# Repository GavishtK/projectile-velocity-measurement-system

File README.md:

# Projectile Velocity Measurement System (PVMS)

> **Development of an IoT-Based Projectile Velocity Measurement System**

---

# 📖 Overview

The **Projectile Velocity Measurement System (PVMS)** is an embedded system designed to accurately measure projectile velocity using the **Optical Time-of-Flight (ToF)** principle.

The system employs two optical sensing gates connected to an **ESP32** microcontroller. As a projectile passes through the sensing gates, the ESP32 records the elapsed time with microsecond precision and calculates the projectile's velocity.

The measured velocity is displayed in real time on an OLED display and simultaneously transmitted through the Serial Monitor for debugging and data logging.

To improve hardware integration and reliability, a **custom PCB was designed using KiCad**, incorporating interfaces for the ESP32, OLED display, optical sensors, laser modules, and power connections.

This project was developed as part of a **summer internship at DRDO**. This repository contains only my original implementation, documentation, and hardware design intended for educational and portfolio purposes. No confidential or restricted information has been included.

---

# 📷 Project Preview

## Hardware Prototype

## OLED Display

## PCB Schematic

## PCB Layout

## PCB 3D Model

---

# ✨ Features

- High-speed projectile velocity measurement
- Optical Time-of-Flight sensing
- ESP32-based embedded system
- Microsecond precision using hardware interrupts
- Real-time OLED display
- Serial Monitor output
- Automatic timeout handling
- Low-cost implementation
- Custom KiCad PCB
- Compact and portable design

---

# ⚙ Hardware Used

| Component | Quantity |
|------------|----------|
| ESP32 DevKit V1 | 1 |
| SSD1306 OLED Display (128×64) | 1 |
| Laser Modules | 2 |
| Photodiodes | 2 |
| Breadboard | 1 |
| Jumper Wires | As Required |
| USB Power Supply | 1 |

---

# 🛠 Software Used

- Arduino IDE
- ESP32 Board Package
- KiCad
- Adafruit SSD1306 Library
- Adafruit GFX Library
- Wire Library

---

# 💻 PCB Design

A custom PCB was designed using **KiCad** to simplify wiring, improve reliability, and provide a compact hardware platform.

### PCB Features

- ESP32 interface
- OLED display connector
- Optical sensor connectors
- Laser module connectors
- Power input connector
- Compact PCB layout
- 3D STEP model included

---

# 🚀 Working Principle

The system consists of two optical sensing gates placed at a fixed distance.

1. The first optical gate detects the projectile.
2. ESP32 starts a high-resolution timer using hardware interrupts.
3. The second optical gate detects the projectile.
4. ESP32 stops the timer.
5. Velocity is calculated using the Time-of-Flight equation.

\[
Velocity = \frac{Distance}{Time}
\]

The calculated velocity is displayed on the OLED screen and transmitted through the Serial Monitor.

---

# 📋 Technical Specifications

| Parameter | Value |
|-----------|-------|
| Controller | ESP32 DevKit V1 |
| Measurement Method | Optical Time-of-Flight |
| Timing Resolution | Microseconds |
| Display | SSD1306 OLED |
| PCB Software | KiCad |
| Firmware | Arduino C++ |

---

# 🧰 Skills Demonstrated

- Embedded Systems
- ESP32 Programming
- Arduino C++
- PCB Design (KiCad)
- Optical Sensor Interfacing
- Hardware Interrupt Programming
- Time-of-Flight Measurement
- Electronic Circuit Design
- Technical Documentation

---

# 📂 Repository Structure

```text
Projectile-Velocity-Measurement-System/
│
├── README.md
├── LICENSE
├── .gitignore
│
├── docs/
│   └── Final_Report.pdf
│
├── src/
│   └── ProjectileVelocityMeasurement.ino
│
├── Images/
│   ├── hardware_setup.jpg
│   ├── oled_display.jpg
│   ├── pvms_schematic.png
│   ├── pvms_pcb_layout.png
│   └── pvms_pcb_3d.png
│
└── pcb/
    ├── pvms.kicad_pro
    ├── pvms.kicad_sch
    ├── pvms.kicad_pcb
    └── pvms.step
```

---

# 📊 Results

The developed prototype successfully measured projectile velocity using optical sensing gates with stable and repeatable measurements.

The system demonstrated:

- Reliable optical triggering
- Accurate microsecond timing
- Stable velocity calculations
- Real-time OLED display
- Successful custom PCB design and 3D model generation

---

# 🔮 Future Improvements

- Rechargeable battery system
- Wireless data logging
- Mobile application
- Cloud connectivity
- 3D-printed enclosure
- Automatic calibration system

---

# 👨‍💻 Author

**Gavisht Karkara**

B.Tech Electronics & Communication Engineering

Thapar Institute of Engineering and Technology

---

# 📜 License

This project is licensed under the MIT License.

---

# ⚠ Disclaimer

This project was developed as part of a summer internship at **DRDO**.

This repository contains only my own implementation, firmware, PCB design, and documentation intended for educational and portfolio purposes. No confidential, proprietary, or restricted information has been included.

## ⭐ If you found this project useful, consider giving it a star!

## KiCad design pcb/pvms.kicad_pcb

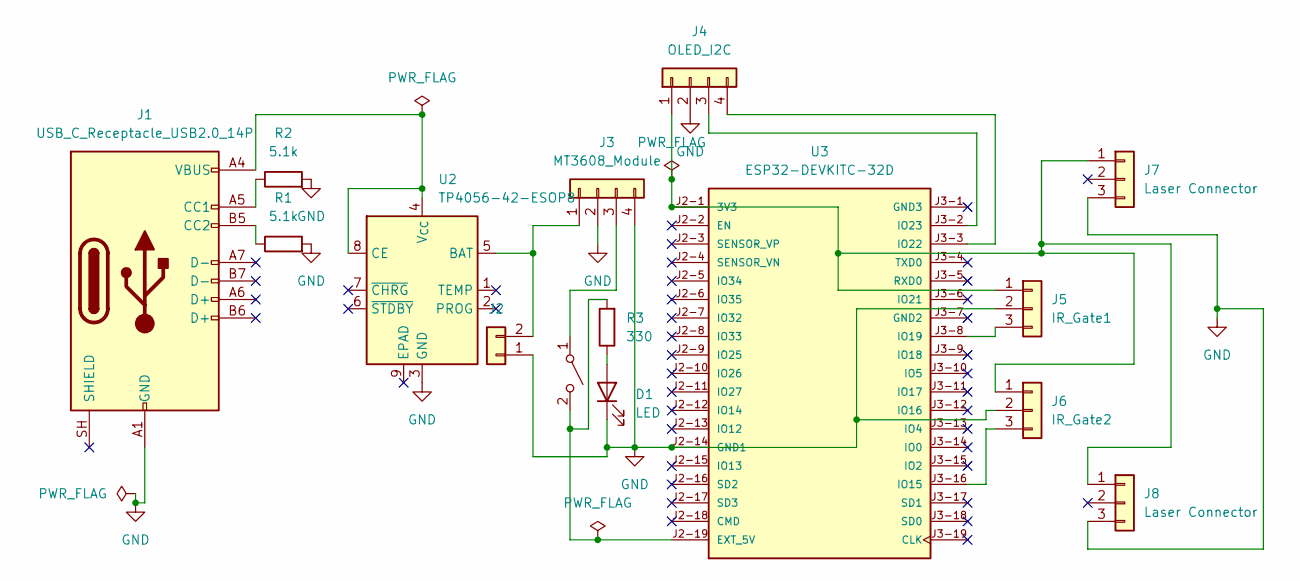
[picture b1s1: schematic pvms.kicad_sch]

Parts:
D1: LED; LED_D5.0mm
J1: USB_C_Receptacle_USB2.0_14P; USB_C_Receptacle_HRO_TYPE-C-31-M-12
J2: Conn_01x02; PinHeader_1x02_P2.54mm_Vertical
J3: MT3608_Module; FanPinHeader_1x04_P2.54mm_Vertical
J4: OLED_I2C; FanPinHeader_1x04_P2.54mm_Vertical
J5: IR_Gate1; FanPinHeader_1x03_P2.54mm_Vertical
J6: IR_Gate2; FanPinHeader_1x03_P2.54mm_Vertical
J7, J8: Laser Connector; FanPinHeader_1x03_P2.54mm_Vertical
R1, R2: 5.1k; R_Axial_DIN0207_L6.3mm_D2.5mm_P7.62mm_Horizontal
R3: 330; R_Axial_DIN0207_L6.3mm_D2.5mm_P7.62mm_Horizontal
SW1: SW_SPST; SW_SPST_B3S-1000
U2: TP4056-42-ESOP8; SOIC-8-1EP_3.9x4.9mm_P1.27mm_EP2.41x3.3mm_ThermalVias
U3: ESP32-DEVKITC-32D; MODULE_ESP32-DEVKITC-32D; PARTREV V4

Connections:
GND: D1.1 (K), J1.A1 (GND), J1.A12 (GND), J1.B1 (GND), J1.B12 (GND), J2.1, J3.2, J3.4, J4.2, J5.2, J6.2, J7.3, J8.3, R1.2, R2.2, U2.3 (GND), U3.J2-14 (GND1)
unnamed: D1.2 (A), R3.1
unnamed: J1.A5 (CC1), R2.1
unnamed: J1.B5 (CC2), R1.1
unnamed: J2.2, J3.1, U2.5 (BAT)
unnamed: J3.3, SW1.1 (A)
unnamed: J4.1, J5.1, J6.1, J7.1, J8.1, U3.J2-1 (3V3)
unnamed: J4.3, U3.J3-2 (IO23)
unnamed: J4.4, U3.J3-3 (IO22)
unnamed: J5.3, U3.J3-8 (IO19)
unnamed: J6.3, U3.J3-16 (IO15)
unnamed: R3.2, SW1.2 (B), U3.J2-19 (EXT_5V)
unnamed: J1.A4 (VBUS), J1.A9 (VBUS), J1.B4 (VBUS), J1.B9 (VBUS), U2.4 (V_{CC}), U2.8 (CE)

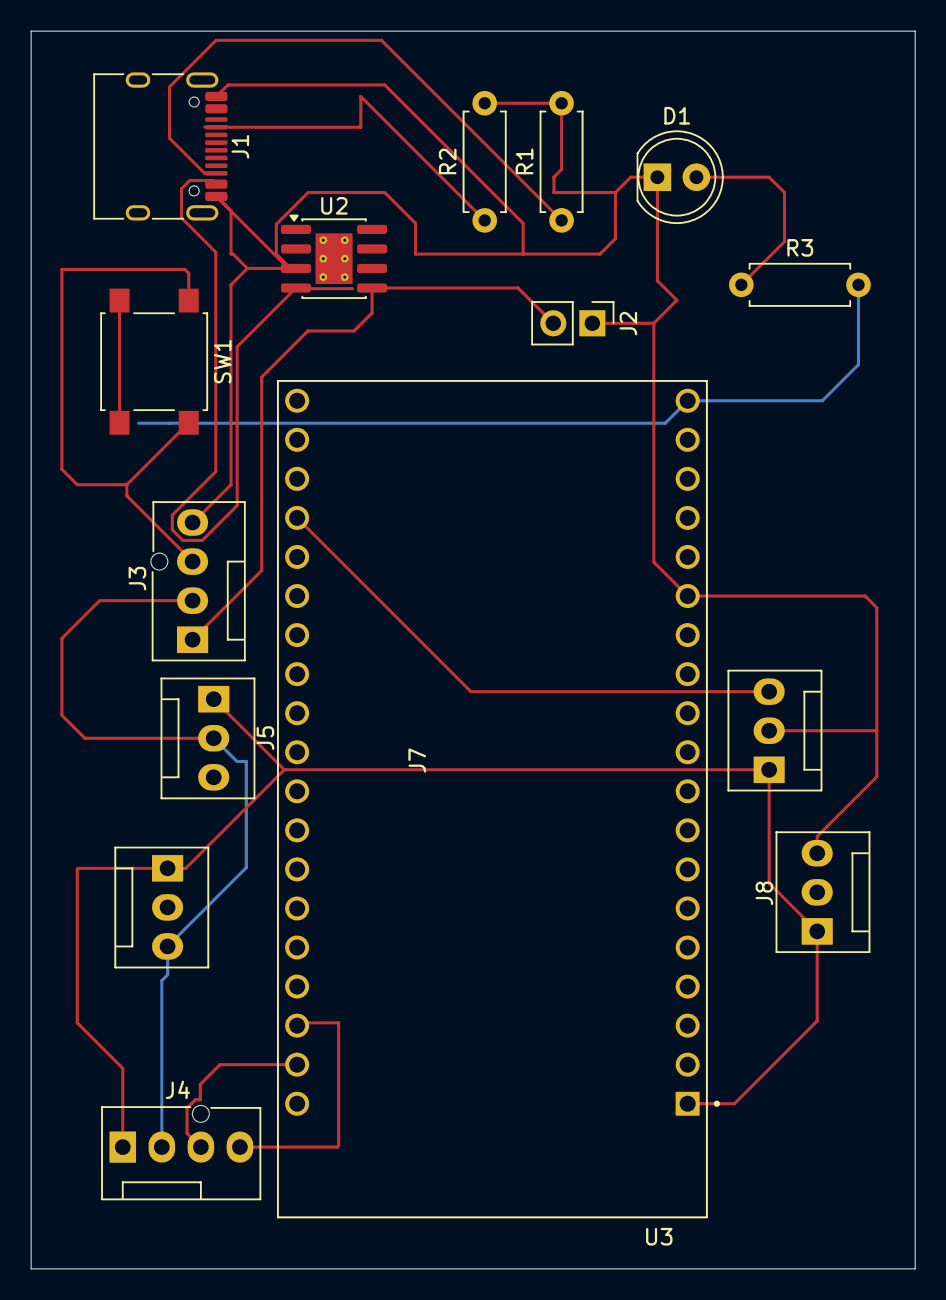
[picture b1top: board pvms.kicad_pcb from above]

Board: 2 copper layers, 57.5 x 80.5 mm, 15 parts (0 on the bottom side), 13 nets.

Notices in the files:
README.md:
License: MIT
